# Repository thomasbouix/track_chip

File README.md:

# TrackChip, le traqueur autonome ! 
L'objectif de ce projet est double :
* Développer un traqueur autonome de précision ~10m (partie Device)
* Récupérer ces informations sur un client WEB (partie Cloud)

### Device
Le device en lui-même est basé sur un micro-controleur ESP32, entouré des périphériques suivant :
* Altimètre BMP180
* GPS ADA746
* Module Sigfox BRKWS01
* Batterie LIPO 1050mAh
* Régulateur de tension 5V Polulu U1V11F5

```
Les sources des bibliothèques des périphériques ainsi que du PCB sont disponibles dans le dossier /devices du git.
```
### Site Web
Le site internet possède les fonctionnalitées suivantes :
* Position de l'utilisateur
* Position du traqueur
* Calcul de la différence d'altitude
* Calcul du trajet en voiture pour rejoindre le traqueur
* Historique des positions du traqueur

```
Les sources du serveur, de la base de donnée et du site Web sont disponibles dans la partie cloud/ du git.
```

# Notice d'utilisation
Le système dans son ensemble possède le comportement suivant :
* Le device utilise le GPS quand il reçoit un signal
* Le device utilise le scrapping WiFi quand le GPS est indisponible
* La position est envoyée sur notre serveur via le réseau SigFox
* Les informations sont accessibles sur notre site via un client Web. 

### Device
Le device s'allume et s'éteint avec le boutton ON/OFF sur le côté de sa boîte protectrice.
Il envoie alors sa position toutes les 5 minutes.
```
Le programme faisant fonctionner le device peut-être modifié et téléversé avec l'IE Arduino.
Il faut simplement s'assurer que les librairies utilisées sont bien visibles en les ajoutant dans ~/Arduino/lib.
```

### Réseau SigFox
Le device envoie ses données sur un backend web en utilisant le réseau SigFox.
Ce backend redirigie ensuite ces informations sur notre serveur grâce à une fonction de callback.
On accède au backend via l'URL suivant :
```
https://backend.sigfox.com/auth/login
```

### Serveur
Le serveur est un ensemble de programmes gérant le site Web ainsi que la base de donnée. 
Il peut être hebergé sur une machine locale, ou bien sur internet via un VPS.
Afin d'avoir accès aux nombreux service de géolocalisation (carte, itinéraire, etc), nous avons utilisé différententes APIs fournies par Google.
Ces APIs nécéssitent une clef pour pouvoir y accéder qu'il faut générer en créant d'abord un compte Google Cloud Platform. 
Puis en copiant-collant cette clef à la place de la notre dans le fichier dev/cloud/php/map.php à la ligne 44 dans le lien du script.
En local, on peut lancer le site avec les commandes suivantes :
```
$ cd /path/to/sources
$ php -S 127.0.0.1.:8888
```

### Site Web
Nous avons choisi d'utiliser l'hébergeur always-data pour notre site.
Cela donnait un URL du type :
```
https://track-chip.alwaysdata.net/
```

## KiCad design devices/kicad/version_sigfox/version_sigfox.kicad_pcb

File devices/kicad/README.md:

# KiCad - Architecture

## Librairie
```
Le fichier track_chip.lib contient tout les "symboles" créés pour le projet :
	- ESP32 NodeMCU
	- BMP180
	- ADA746
	- BRKWS01

La librairie contient aussi les symboles déjà présents par défaut dans KiCad, 
afin d'éliminer la dépendance à la version du logiciel.
```

## Schéma
```
Le fichier .sch représente le schéma du circuit électronique du système (Eeschema).
Il instancie les différents symboles de la librairie du projet.
```

## Empreintes

### Dimensions
```
- Largeur typique d'une piste : 1mm
- Largeur typique d'une alimentation : 2mm
- Ecart entre les pastilles : 2.54mm
- Diamètre typique de perçage : 0.8mm
- Diamètre typique de pastille : 1.5mm
```

### Plans de masse
```
Recommendations : faire des plans de masses.
Si il y a un domaine analogique et un domaine numérique, 
faire des plans de masse séparés et les relier avec une piste.
```

## Batterie
```
On utiliser un circuit avec chargeur intégré.
```

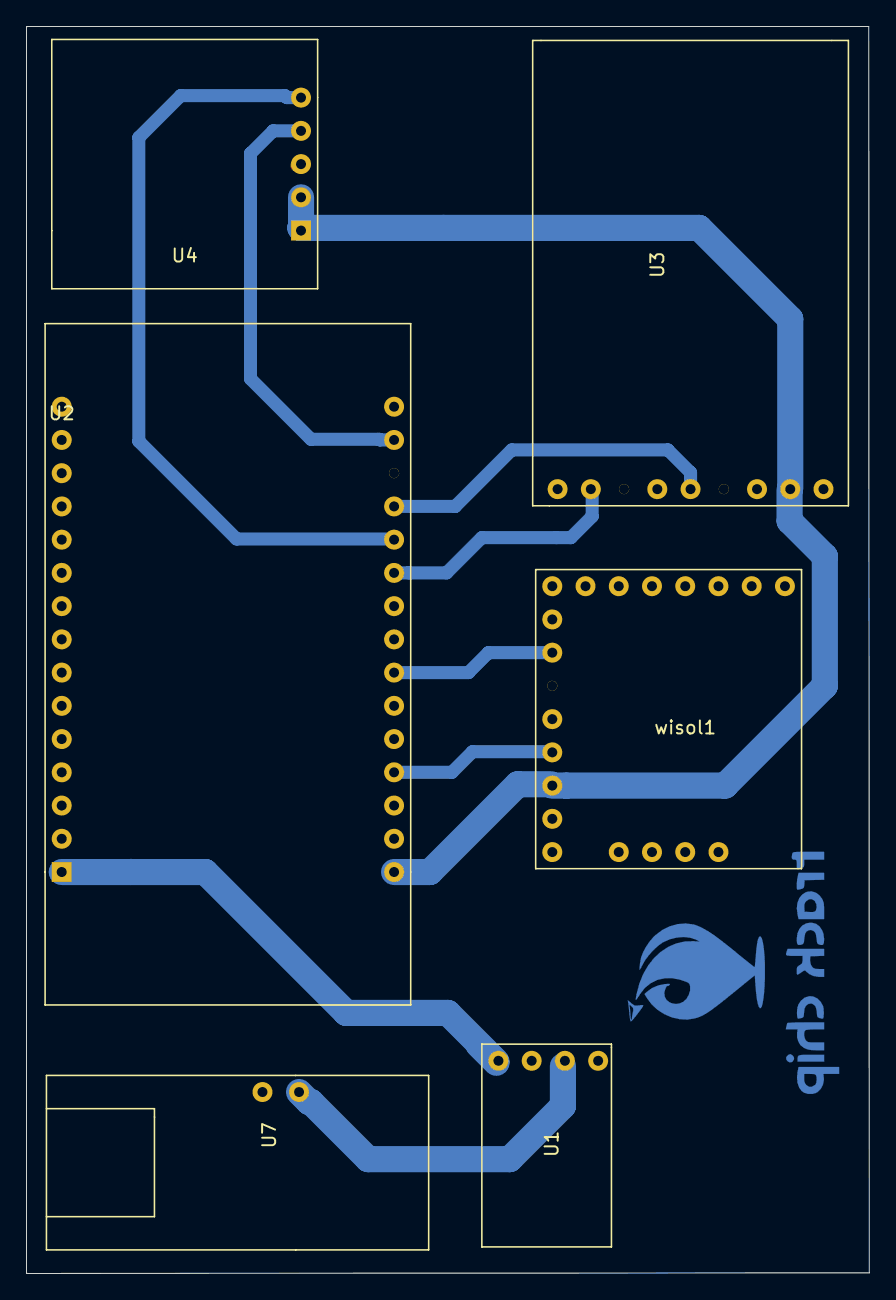
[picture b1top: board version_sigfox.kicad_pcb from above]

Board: 2 copper layers, 64.4 x 95.3 mm, 6 parts (0 on the bottom side), 10 nets.

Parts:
U1: polulu
U2: esp32_NodeMCU-track_chip; esp32
U3: GPS_PA6H
U4: bmp180-track_chip; bmp180
U7: charger_mr010
wisol1: brkws01; BRWS01

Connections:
3V3: U2.16, U3.8, U4.1, U4.2, wisol1.6
5V: U1.4, U2.15
EN_GPS: U2.25, U3.2
GND: U1.3, U2.17, U3.7, U4.3, U7.2, wisol1.7
GPS_TX0: U2.27, U3.5
MCU_TX2: U2.22, wisol1.2
RST_WSL: U2.19, wisol1.5
SCL: U2.29, U4.4
SDA: U2.26, U4.5
VBAT: U1.2, U7.1

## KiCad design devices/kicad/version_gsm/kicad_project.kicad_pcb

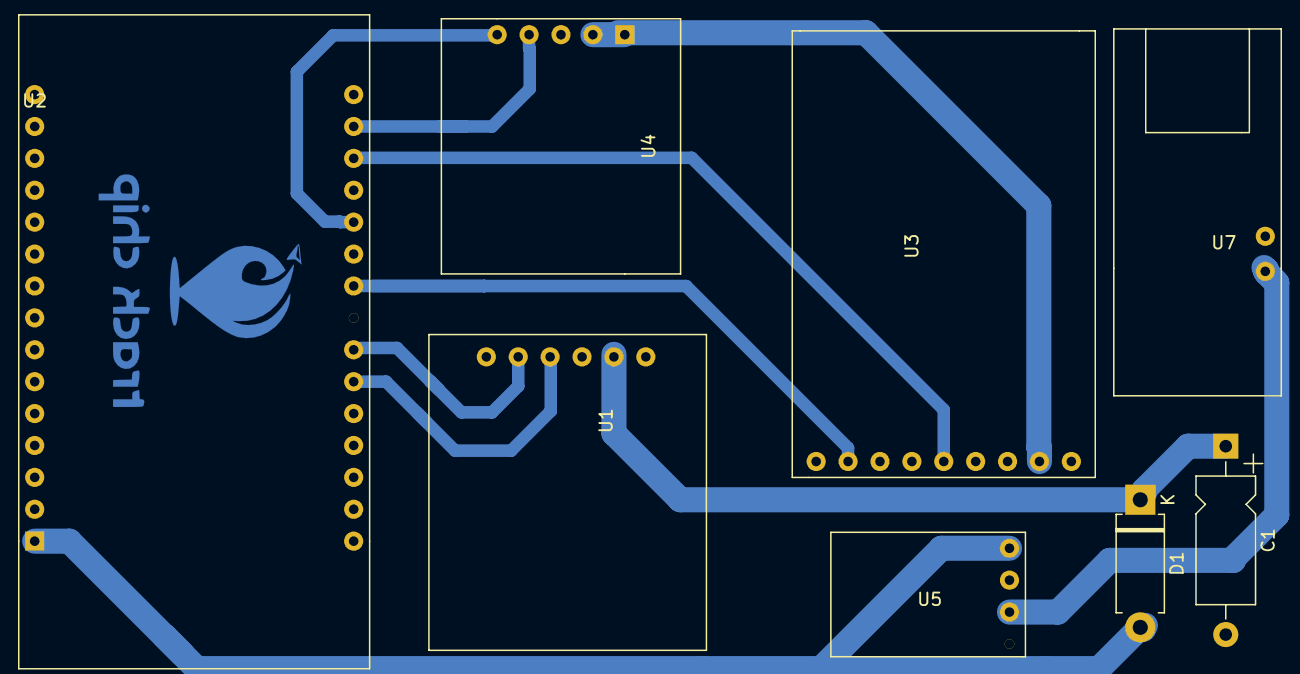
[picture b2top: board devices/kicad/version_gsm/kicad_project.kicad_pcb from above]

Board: 2 copper layers, 8 parts (0 on the bottom side), 11 nets.

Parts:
C1: 100u; CP_Axial_L10.0mm_D4.5mm_P15.00mm_Horizontal
D1: 0.8V; D_DO-15_P10.16mm_Horizontal
U1: SIM800L
U2: esp32_NodeMCU-track_chip; esp32
U3: GPS_PA6H
U4: bmp180-track_chip; bmp180
U5: polulu
U7: charger_mr010

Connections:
3.3V: U3.8, U4.1, U4.2
5V: D1.2, U2.15, U5.4
EN_GPS: U2.24, U3.2
GND: C1.2, U1.6, U2.17, U3.7, U4.3, U5.3, U7.2
unnamed: C1.1, D1.1, U1.2
RX2: U1.4, U2.21
SCL: U2.29, U4.4
SDA: U2.26, U4.5
TX0: U2.28, U3.5
TX2: U1.5, U2.22
VBAT: U5.2, U7.1

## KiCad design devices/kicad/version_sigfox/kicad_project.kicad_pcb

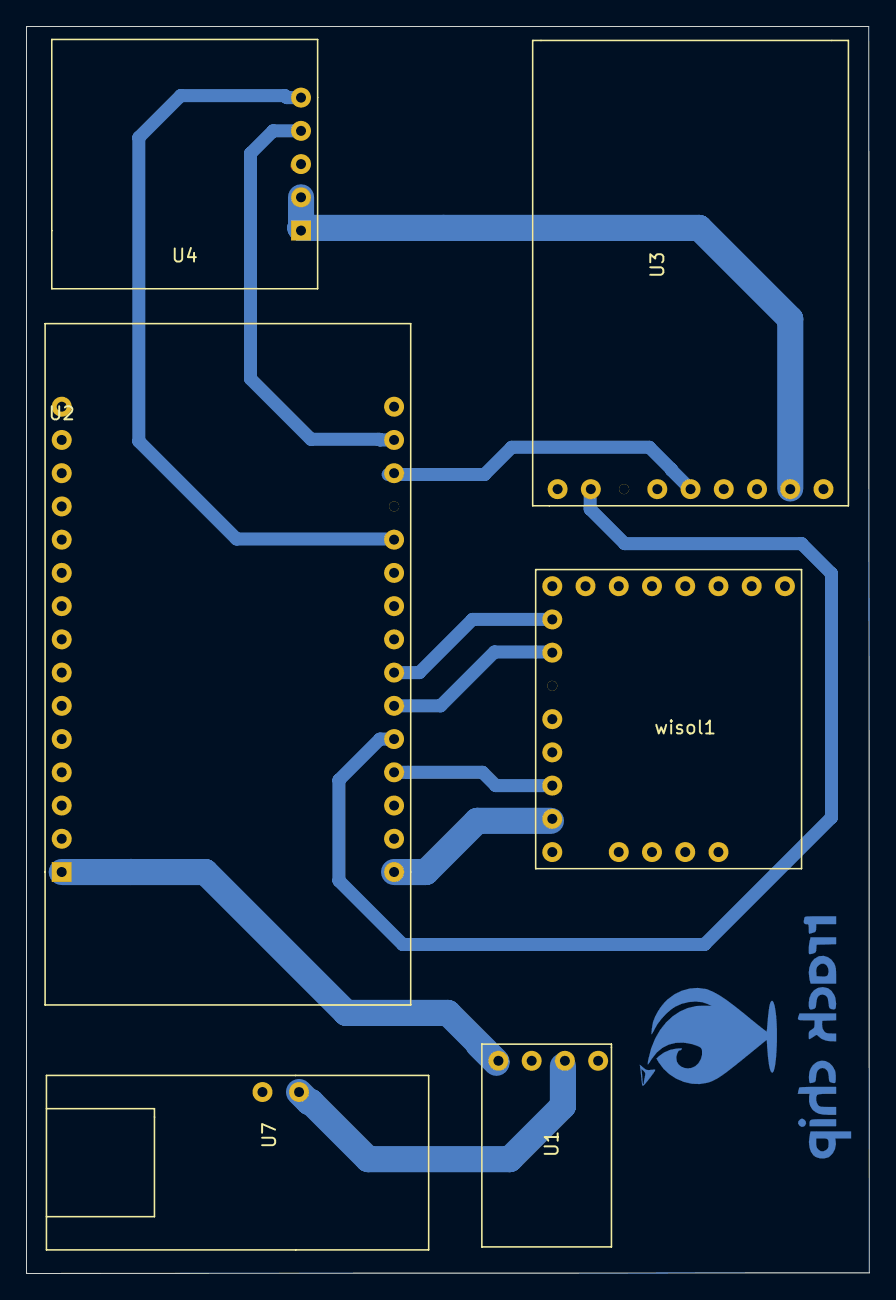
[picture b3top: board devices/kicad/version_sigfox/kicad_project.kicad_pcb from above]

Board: 2 copper layers, 64.4 x 95.3 mm, 6 parts (0 on the bottom side), 12 nets.

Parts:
U1: polulu
U2: esp32_NodeMCU-track_chip; esp32
U3: GPS_PA6H
U4: bmp180-track_chip; bmp180
U7: charger_mr010
wisol1: brkws01; BRWS01

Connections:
3.3V: U3.8, U4.1, U4.2
3V3: U2.16, wisol1.7
5V: U1.4, U2.15
EN_GPS: U2.20, U3.2
GND: U1.3, U2.17, U3.7, U4.3, U7.2, wisol1.8
RST_WSL: U2.19, wisol1.6
RX2: U2.21, wisol1.2
SCL: U2.29, U4.4
SDA: U2.26, U4.5
TX0: U2.28, U3.5
TX2: U2.22, wisol1.1
VBAT: U1.2, U7.1

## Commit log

2021-01-18 bmp init commit
2021-01-18 add start codes for testing grove gps
2021-01-19 ajout squlette driver bmp180 + scanner i2c
2021-01-19 adding markdown format
2021-01-21 adding commentaries
2021-01-21 bcm180 is working
2021-01-21 envoie sigfox et verification longeure/hexa
2021-01-21 correcting bmp180/README
2021-01-21 add source files
2021-01-21 add README.md for accelerometre_mma8451
2021-01-21 altitude succesfully mesured
2021-01-21 add library
2021-01-21 add source code brut data and line data
2021-01-21 modification librairie
2021-01-21 function BCM::computeAltitude() is compiling
2021-01-21 adding init function, modifying altitude formula
2021-01-21 packaging librarie + instructions in README
2021-01-21 cleaning repo
2021-01-22 refactoring
2021-01-23 refactoring suivi recommendation Thomas
2021-01-24 init kicad branch
2021-01-24 update kicad/README
2021-01-26 ajout brkws01
2021-01-29 corrections review enzo
2021-01-31 files structure
2021-01-31 add header class for gps
2021-01-31 update header
2021-01-31 add source file for class
2021-01-31 update examples
2021-01-31 renomage Wisol.cpp
2021-01-31 renomage Wisol.h
2021-01-31 ajout commentaire Wisol.cpp
2021-01-31 ajout README
2021-02-01 correct indentation
2021-02-01 change device to devices
2021-02-01 ajout GPS ADA746
    + encapsulation de tous les composants dans la librairie du projet
2021-02-01 adding bmp180 to system
2021-02-01 modification des includes de l'example
2021-02-01 patch lib grove11302 + ajout au system
2021-02-01 patch virtual destructor bug in grove11302, patch bug d'instanciation d'objet
2021-02-01 refactoring file structure, adding wisol to system
2021-02-01 encapsuling into TrackChip class, closes #15
2021-02-01 renaming files
2021-02-01 add Arduino WiFi librairy
2021-02-01 add wifi scan example
2021-02-02 system bug fixed => using new() to do dynamic allocation
2021-02-03 modify Adafruit_MMA8451 lib by adding init and computeAcceleration functions
2021-02-03 adding example code
2021-02-03 refactoring file structure
2021-02-03 no message with wisol, division by 0 on bmp180
2021-02-03 bug with pointers
2021-02-03 bug sigox understood
2021-02-03 deleted WiFi librairy
2021-02-03 update_final_example
2021-02-03 add README for install dependancies
2021-02-04 define the expectation
2021-02-04 definition fonctions
2021-02-04 update-scan_post-add_json_parse
2021-02-04 update-wifi_scan
2021-02-04 update-https_client
2021-02-04 add gitignore
2021-02-04 system is working
2021-02-04 dev-wifi_scanner-all_functions_in_files
2021-02-04 refactoring trackChip
2021-02-04 deleting /https_post/.DS_Store
2021-02-04 double_to_int, double_to_hexa
2021-02-04 Dms_to_dd
2021-02-04 Test assemblage des fonctions : int_to_hexa bug pour nombre négatif
2021-02-04 move wifi_esp32/ into position/ folder
2021-02-04 complete_hexa_bytes
2021-02-04 encapsulation fonctions
2021-02-04 refactoring :ajout des fonctions dans la classe sigfox
2021-02-04 integration wifi en cours
2021-02-04 wifi is integrated
2021-02-04 refactoring ident
2021-02-06 add example /refactoring
2021-02-07 example->examples ajout dossier
2021-02-07 suppression double setup/loop
2021-02-08 rename example main_wisol
2021-02-08 supression example en doublon
2021-02-08 modify_network_filtering
2021-02-08 modify wifi_scan function
2021-02-08 adding fingerprints
2021-02-08 add first version of website
2021-02-08 more fingerprints and symbols
2021-02-08 add altitude in HTML file
2021-02-08 add sql file
2021-02-08 errors fixed
2021-02-09 Refactoring local structure
2021-02-09 [PCB] Premier jet
2021-02-10 update-gitignore
2021-02-10 dev-map-add_sql_comm
2021-02-10 refactoring-separate_css_from_php
2021-02-10 refactoring-separate_js_from_php
2021-02-10 update-gitignore-delete_sqlile
2021-02-10 [PCB] version sim en cours
2021-02-10 version_sim => version_gsm
2021-02-10 Initing sigfox branch
2021-02-10 update-php
2021-02-10 [PCB] Premier jet Sigfox
2021-02-10 [PCB] Ajout logo
2021-02-10 update-README-alwaysdata-ssh_key
2021-02-10 [PCB] Routage terminé + ajout logo
2021-02-10 update-REAMDE-alwaysdata
2021-02-10 dev-README-cloud
2021-02-10 add-logo
2021-02-10 [PCB] Ajout du plan de coupe
2021-02-10 [PCB] Ajout du plan de masse
2021-02-10 ajout fonction verif_type
2021-02-10 [PCB] Création des fichiers gerbers
2021-02-10 test de la fonction a encapsuler
2021-02-10 [PCB] Premier jet GSM
2021-02-11 lecture d'un caractère
2021-02-11 récupération latitude
2021-02-11 Fixing sigfox ver
2021-02-11 fusion récupération, lat, lng à partir de la trame
2021-02-11 création function encapsulation lat/lng
2021-02-11 test de GPGGA_to_DMS ok
2021-02-11 [PCB] update version gsm
2021-02-11 trame_GPGGA_to_DMS compile
2021-02-11 test fonction trame_GPGGA_to_DMS
2021-02-11 Refactoring : déplacement de l'exemple
2021-02-11 update-renamed_css_file
2021-02-11 update-renamed_icon_file
2021-02-11 update-renamed_main_php_file
2021-02-11 update-map_js-handle_map
2021-02-11 dev-datas_js
2021-02-11 update-sql-change_order_field
2021-02-11 dev-php-side_files
2021-02-11 ajout de l'envoie de la trame
2021-02-11 send_trame : conversion et envoie de la trame
2021-02-11 supression commentaire
2021-02-11 modif de fonction TrackChip::send_data(String s)
2021-02-11 modif pour callback enzo
2021-02-12 update-sigfox_php-formalize_sigfox_data
2021-02-12 dev-sql-add_user_login
2021-02-12 update-index_php-logIn_page
2021-02-12 dev-login_css
2021-02-12 dev-login_php-check_logIn_values
2021-02-12 test_fork
2021-02-14 ajout string en int dans le bon ordre
2021-02-14 dev-login_css-anim
2021-02-14 demonstration+ affichage des fonctions de conversion
2021-02-14 update-sql_file
2021-02-14 dev-index_php-error_auth
2021-02-14 update-map_js-add_default_current_alt
2021-02-14 dev-login_php-add_redirections
2021-02-14 update-map_php-correct_js_paths
2021-02-14 update-login_php-redirect_to_alwaysdata
2021-02-14 update-login_php-correct_redirection_to_alwaysdata
2021-02-14 dev-map_js-add_itinerary_functions
2021-02-14 dev-map_js-add_address
2021-02-14 dev-sql-add_fake_path
2021-02-14 update-datas_js-add_parameters_for_path
2021-02-14 update-datas_php-change_sqlite_request_for_path
2021-02-14 dev-map_js-add_marker_path_features
2021-02-15 update-map_js-add_variable
2021-02-15 update-datas_php-add_comments
2021-02-15 update-sigfox_php-formulae
2021-02-15 update-map_js-correct_taping_error
2021-02-15 update-php_files-script_execute
2021-02-15 dev-database_sh
2021-02-15 dev-map_php-add_span_arrow
2021-02-15 dev-map_js-add_diff_alt
2021-02-15 utilisation fonction send_trame
2021-02-15 indentation
2021-02-15 update-map_php-add_span_time_dist
2021-02-15 update-php_database-comment_script_execution
2021-02-15 dev-map_js-add_distance_matrix
2021-02-15 update-map_js-add_marge_alt
2021-02-15 add type bssid
2021-02-15 fixing sigfox pcb
2021-02-15 ajout getter
2021-02-15 création receive_fix() à implémenter
2021-02-15 signature new function
2021-02-15 function needs to be define in trackchip
2021-02-16 correction symbole + empreinte sigfox
2021-02-16 numérotation du wisol dans le eeschema
2021-02-16 refactoring code, updating system README
2021-02-16 changement de structure
2021-02-16 create_message1
2021-02-16 test function create_message1()
2021-02-16 test concluant trackChip.create_message2();
2021-02-16 TrackChip::create_message3()
2021-02-16 modif pour tester TrackChip::create_message3()
2021-02-17 receive_fix() à coder
2021-02-17 chose_message_to_send
2021-02-17 sauvegarde des bssid BD : optimal pour la démo
2021-02-17 comment unused part
2021-02-17 Refactoring : put Trackchip files at the right place
2021-02-17 Refactoring : Grove .cpp at the right place
2021-02-17 file moved at the right place
2021-02-17 README.md
2021-02-17 commenting debug
2021-02-17 ajout de la puissance dans les messages
2021-02-17 harmonisation taille du message : 20 char
2021-02-17 function part_bssid_to_hexa : encapsulation adresse mac en hexa
2021-02-17 Test part_bssid_to_hexa
2021-02-17 dev-sql-add_WiFiEndpoint_table
2021-02-17 update-sql-add_device_id_field
2021-02-17 dev-sigfox_php-refactoring_all_format_from_sigfox
2021-02-18 first backup
2021-02-18 backup 2
2021-02-18 update-sigfox_php-correct_format_gps_messge
2021-02-18 backup 3
2021-02-18 update-map_js-increase_nb_positions_display
2021-02-18 update-sigfox_php-change_callback_format
2021-02-18 receive_fix
2021-02-18 modif signature receive_fix())
2021-02-19 update-map_js-nb_positions_display
2021-02-19 update-database
2021-02-19 update-database-nb_positions
2021-02-19 update-map-correction
2021-02-20 update cloud/README
2021-02-21 update-data_js-correct_receive_format
2021-02-21 refactoring code
2021-02-21 system/examples/ are compiling
2021-02-21 update-map_js-reformat_nb_positions_display
2021-02-21 update-README
